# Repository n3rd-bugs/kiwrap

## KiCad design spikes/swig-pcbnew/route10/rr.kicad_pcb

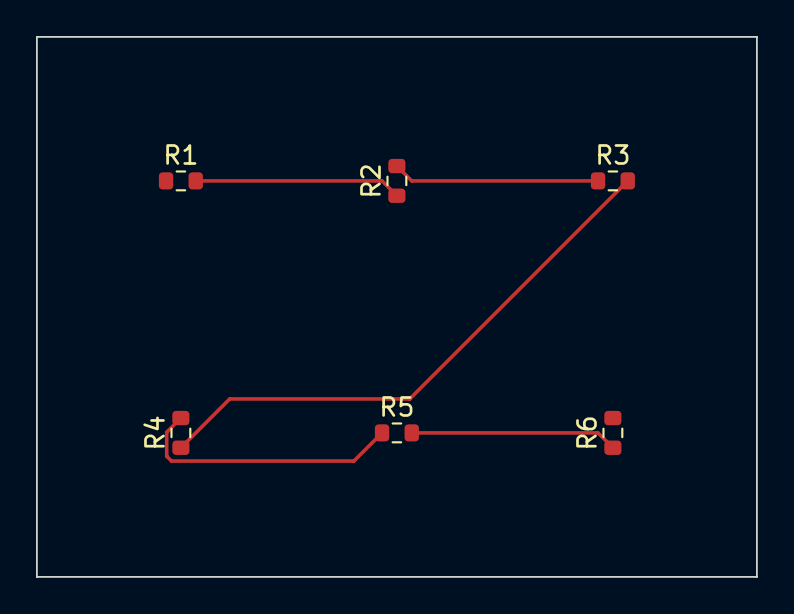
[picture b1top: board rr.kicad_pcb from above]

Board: 2 copper layers, 40.0 x 30.0 mm, 6 parts (0 on the bottom side), 5 nets.

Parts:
R1, R2, R3, R4, R5, R6: 1k; R_0603_1608Metric

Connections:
N2: R1.2, R2.1
N3: R2.2, R3.1
N4: R3.2, R4.1
N5: R4.2, R5.1
N6: R5.2, R6.1
